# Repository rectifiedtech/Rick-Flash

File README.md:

# Rick Flash v1.0

### Watch it in action

https://youtu.be/qJRm4iVWZss

Here's a link to the limited production run of the Rick Flash project - https://www.ebay.com/itm/264855847576 - We might not make anymore of these unless there's more demand.

## Getting Started
1. Insert Rick Flash into an M.2 SSD slot, works with both SATA and NVME SSD slots (B+M Key), keep in mind that the module is a little wider and thicker than a standard M.2 SSD and may not fit in all laptops and desktops perfectly.
2. If the Rick Flash does not make any sound then slide the switch on the side of the M.2 module and try again, you should hear the tune start to play.

## WiFi Connection
### (MAY NOT WORK WITH SOME SAMSUNG PHONES)
When the Rick Flash is powered on it will play a short tune to the Rick Roll song known as “Never Gonna Give You Up” by Rick Astley (you probably already figured this out by now). The Rick Flash creates a WiFi access point called “Free WiFi!”, when connected to it via a phone or computer you will be redirected to a captive portal web page (you may have to tap on “Sign in to Free WiFi!”) on the device that displays “You Got Rick Rolled!!!” with a GIF of Rick Astley along with the lyrics to the song. You can also trigger the song to replay using the web page interface (See Below).

## Remote control over WiFi
1. Power on the Rick Flash and wait until the song stops playing.
2. Connect to the WiFi network called “Free WiFi!” and you should be redirected to a page with a GIF of Rick Astley.
3. Click on the hyperlink called “Click here to trigger the Rick Flash!” and it will replay the song on the Rick Flash remotely. Keep in mind that the WiFi connection may drop out during the song playback and you can only trigger it to replay after the song finishes.

## Programming Pads
The Rick Flash can be reprogrammed using the Arduino IDE and connecting the appropriate pins from a WEMOS D1 Mini Board (without the ESP module soldered) to the programming pads on the back of the M.2 module.

### Programming the ESP8266
Connect a headless WEMOS D1 Mini board to the Programming pads then upload your code using the arduino IDE with the WEMOS D1 Mini Board selected. Also make sure to write the html and image files to the ESP8266 via SPIFFS by selecting Tools --> ESP8266 Sketch Data Upload. You may need to add the ESP8266 boards to your boards manager as well as the libraries used in the original Arduino code.

## Bill of Materials
|     |                                   |         |                                                                                                                         | 
|-----|-----------------------------------|---------|-------------------------------------------------------------------------------------------------------------------------| 
| Qty | Description                       | LCSC #  | Link                                                                                                                    | 
| 1   | PCB                               | -       | Manufacturer of choice                                                                                                  | 
| 1   | ESP-12E                           | C89297  | https://lcsc.com/product-detail/WIFI-Modules_ESP-12E_C89297.html                                                        | 
| 1   | Piezo Buzzer MLT-8530             | C94599  | https://lcsc.com/product-detail/Buzzers_Jiangsu-Huaneng-Elec-MLT-8530_C94599.html                                       | 
| 1   | SMD Slide Swith MSK12C02          | C431540 | https://lcsc.com/product-detail/Toggle-Switches_SHOU-HAN-MSK12C02_C431540.html                                         | 
| 9   | Padauk Microcontroller PMS152-S16 | C317590 | https://lcsc.com/product-detail/PADAUK_PADAUK-Tech-PMS152-S16_C317590.html                                              | 
| 4   | 10k 0805 Resistor                 | C343942 | https://lcsc.com/product-detail/Chip-Resistor-Surface-Mount_FH-Guangdong-Fenghua-Advanced-Tech-RC-05K103JT_C343942.html | 
| 1   | 1uF 0805 Capacitor                | C344171 | https://lcsc.com/product-detail/Others_CCTC-TCC0805X7R105K250DTS_C344171.html                                           |

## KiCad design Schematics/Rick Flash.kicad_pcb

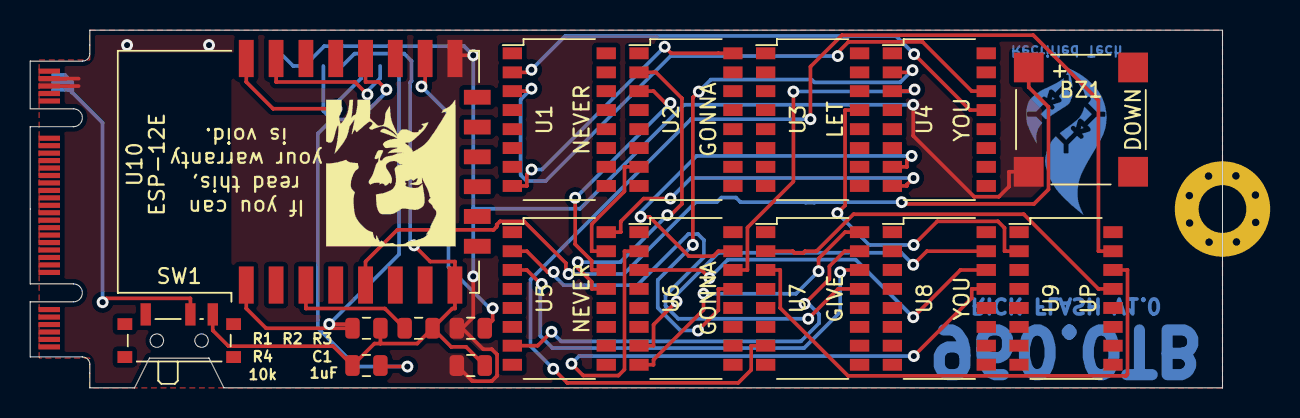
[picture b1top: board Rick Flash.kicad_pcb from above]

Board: 2 copper layers, 80.0 x 24.0 mm, 20 parts (1 on the bottom side), 35 nets.

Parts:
BZ1: Buzzer; PUIAudio_SMT_0825_S_4_R
C1: 1uF; C_0805_2012Metric
H1: MountingHole; MountingHole_3.2mm_M3_Pad_Via
J1: M.2 Edge Connector; NGFF_B+M
J2: ICSP_NODEMCU; 6pin 1.27mm ICSP Pad
R1, R2, R3, R4: 10k; R_0805_2012Metric
SW1: POWER SW; SW_SPDT_PCM12
U1, U2, U3, U4, U5, U6, U7, U8, U9: 4017; SOP-16_4.4x10.4mm_P1.27mm
U10: ESP-12E

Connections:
+3V3: J1.70, J1.72, J1.74, SW1.2
ESP_3V3: C1.1, J2.3, R1.2, R2.2, R4.1, SW1.3, U10.8
GND: BZ1.2, C1.2, J1.71, J1.73, J2.1, R3.1, U10.15
GPIO-0: J2.2, R4.2, U10.18
unnamed: BZ1.1, U10.5
unnamed: R2.1, U10.3
unnamed: R3.2, U10.16
unnamed: U1.2, U4.13
unnamed: U1.3, U4.14
unnamed: U1.7, U4.15
unnamed: U1.8, U2.16
unnamed: U2.2, U5.13
unnamed: U2.3, U5.14
unnamed: U2.7, U5.15
unnamed: U3.13, U9.2
unnamed: U3.14, U9.3
unnamed: U3.15, U9.7
unnamed: U4.2, U6.13
unnamed: U4.3, U6.14
unnamed: U4.7, U6.15
unnamed: U4.8, U5.16
unnamed: U5.2, U7.13
unnamed: U5.3, U7.14
unnamed: U5.7, U7.15
unnamed: U6.2, U8.13
unnamed: U6.3, U8.14
unnamed: U6.7, U8.15
unnamed: U6.8, U7.16
unnamed: U7.2, U9.13
unnamed: U7.3, U9.14
unnamed: U7.7, U9.15
unnamed: U8.8, U9.16
RESET: J2.6, R1.1, U10.1
RX: J2.5, U10.21
TX: J2.4, U10.22

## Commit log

2020-08-22 Update LICENSE
